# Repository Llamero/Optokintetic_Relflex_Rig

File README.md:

# Optokinetic Reflex Behavior Rig
 This is an open-source behavior rig designed to accurately the optokinetic reflex in mice.  This design is a derivative of the following designs:
 * https://pmc.ncbi.nlm.nih.gov/articles/PMC10023158/
 * https://www.jneurosci.org/content/37/5/1102
 
 The development of this scope and illuminator was funded by the following grant: NIH P30EY003176

## How to use the CAD files
The CAD files can be opened using FreeCAD: https://www.freecadweb.org/downloads.php  Unless otherwise specified, all the part numbers listed in the CAD file are Thorlabs part numbers.

## Controlling the LEDs
The green (l-cone) and UV (s-cone) 27 amp LEDs are directly controlled via the RGB LED control channels on the EKB DLP.  These 3v3 outputs are shifted to 12V with a gate driver, which is then used to switch mosfets in series with the LEDs.  Ballast resistors control the current.

All circuit design files can be found in the KiCAD filder, and opened using KiCAD: https://www.kicad.org/download/

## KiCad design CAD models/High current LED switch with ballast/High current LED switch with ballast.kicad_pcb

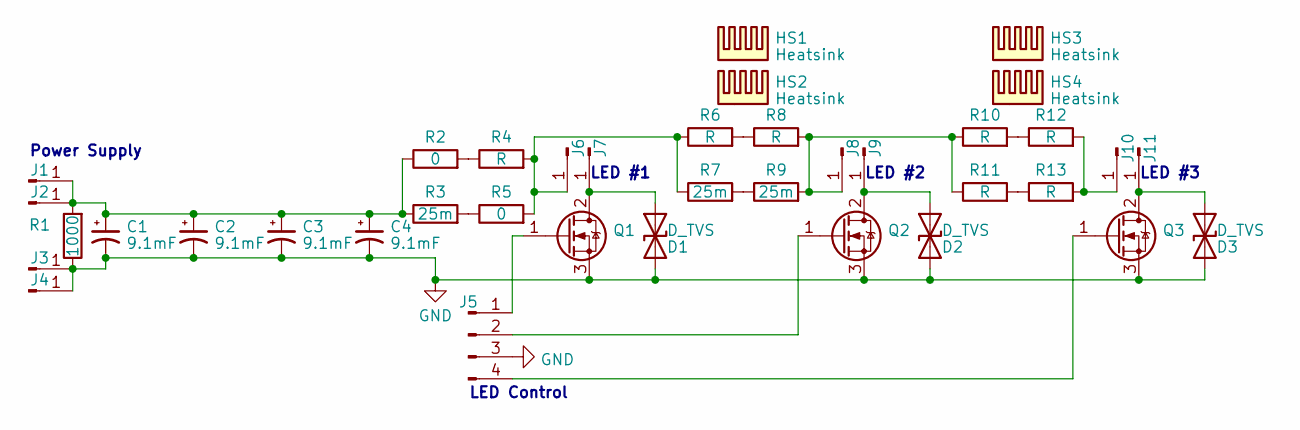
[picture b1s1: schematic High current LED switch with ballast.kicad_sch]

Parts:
C1, C2, C3, C4: 9.1mF; CAP_FKS_K21_PAN; Part EEE-FK1A912SM
D1, D2, D3: D_TVS; DO-214AB; Part SMDJ60A/TR13
HS1, HS2, HS3, HS4: Heatsink; 31mm heatsink; Part 906-31-2-23-2-B-0
J1, J2, J3, J4, J6, J7, J8, J9, J10, J11: Conn_01x01_Pin; KEYSTONE_4928; Part 4928
J5: Conn_01x04_Pin; PinHeader_1x04_P2.54mm_Vertical_SMD_Pin1Right; Part M20-8770442
Q1, Q2, Q3: Q_NMOS_GDS; TO-263-2; Part GT035N10M
R1: 1000; R_1206_3216Metric; Part RMCF1206FT1K00
R2, R5: 0; R_2818; Part TLRZ2BTTD
R3, R7, R9: 25m; R_2818; Part WSHP2818R0250FEA
R4, R6, R8, R10, R11, R12, R13: R; R_2818

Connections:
GND: C1.2, C2.2, C3.2, C4.2, D1.2 (A2), D2.2 (A2), D3.2 (A2), J3.1, J4.1, J5.3, Q1.3 (S), Q2.3 (S), Q3.3 (S), R1.1
unnamed: D1.1 (A1), J7.1, Q1.2 (D)
unnamed: D2.1 (A1), J9.1, Q2.2 (D)
unnamed: D3.1 (A1), J11.1, Q3.2 (D)
unnamed: C1.1, C2.1, C3.1, C4.1, J1.1, J2.1, R1.2, R2.1, R3.1
unnamed: J5.1, Q1.1 (G)
unnamed: J5.2, Q2.1 (G)
unnamed: J5.4, Q3.1 (G)
unnamed: J6.1, R4.2, R5.2, R6.1, R7.1
unnamed: J8.1, R8.2, R9.2, R10.1, R11.1
unnamed: J10.1, R12.2, R13.2
unnamed: R2.2, R4.1
unnamed: R3.2, R5.1
unnamed: R6.2, R8.1
unnamed: R7.2, R9.1
unnamed: R10.2, R12.1
unnamed: R11.2, R13.1

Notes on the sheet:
LED #1
Power Supply
LED #3
LED Control
LED #2

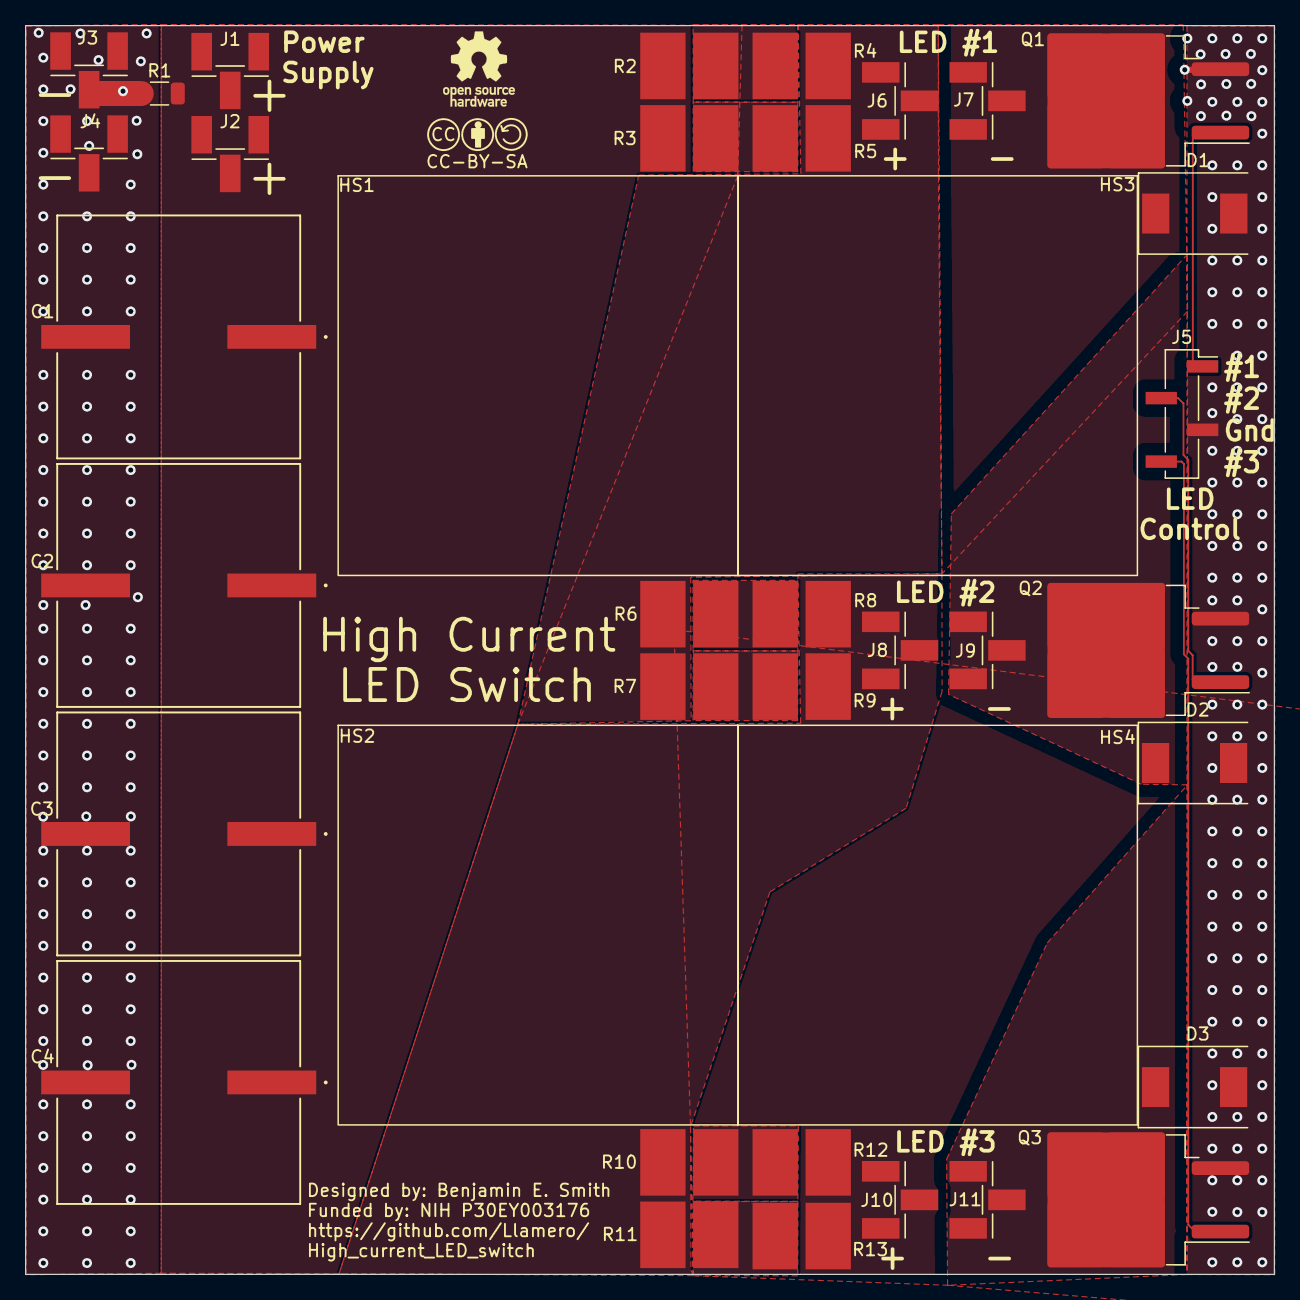
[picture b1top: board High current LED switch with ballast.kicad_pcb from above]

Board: 2 copper layers, 100.0 x 100.0 mm, 38 parts (0 on the bottom side), 17 nets.

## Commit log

2024-03-03 First 3 camera test
2024-03-04 Class vectors!
    Using class pointer vectors to list devices
2024-03-05 Three initialize - boot only camera 1
2024-03-05 Add Class wide selection index variable to track camera selected
2024-03-07 All cameras record, playback doesn't update view.
2024-03-09 Change buffer size for all 3 cameras
2024-03-09 Moving slider updates view, playback works
2024-03-16 Cameras now synced by having one camera trigger the other two.
2024-03-19 Initial code for streaming to hard drive
2024-03-26 Add arduino code for controlling LEDs
2024-03-26 Fix pins - add 3rd fan
2024-04-04 GUI control
2024-04-04 add python code
2024-04-11 Add alarm
2024-05-08 Fix CM1-DCH fan add Python code to repository
2024-05-08 GUI draft - distinguish nIR cameras from vis camera by text
2024-05-09 Programs close with controller window
2024-05-10 GUI map and events added
2024-07-27 Automate buffer
2024-07-30 Save movie and metadata added
2025-02-03 Add OKR rig models to repository
2025-02-03 add images
2025-02-06 Add KiCAD files

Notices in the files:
parts and their libraries:
CC-BY-SA Symbol
CC-BY-SA
